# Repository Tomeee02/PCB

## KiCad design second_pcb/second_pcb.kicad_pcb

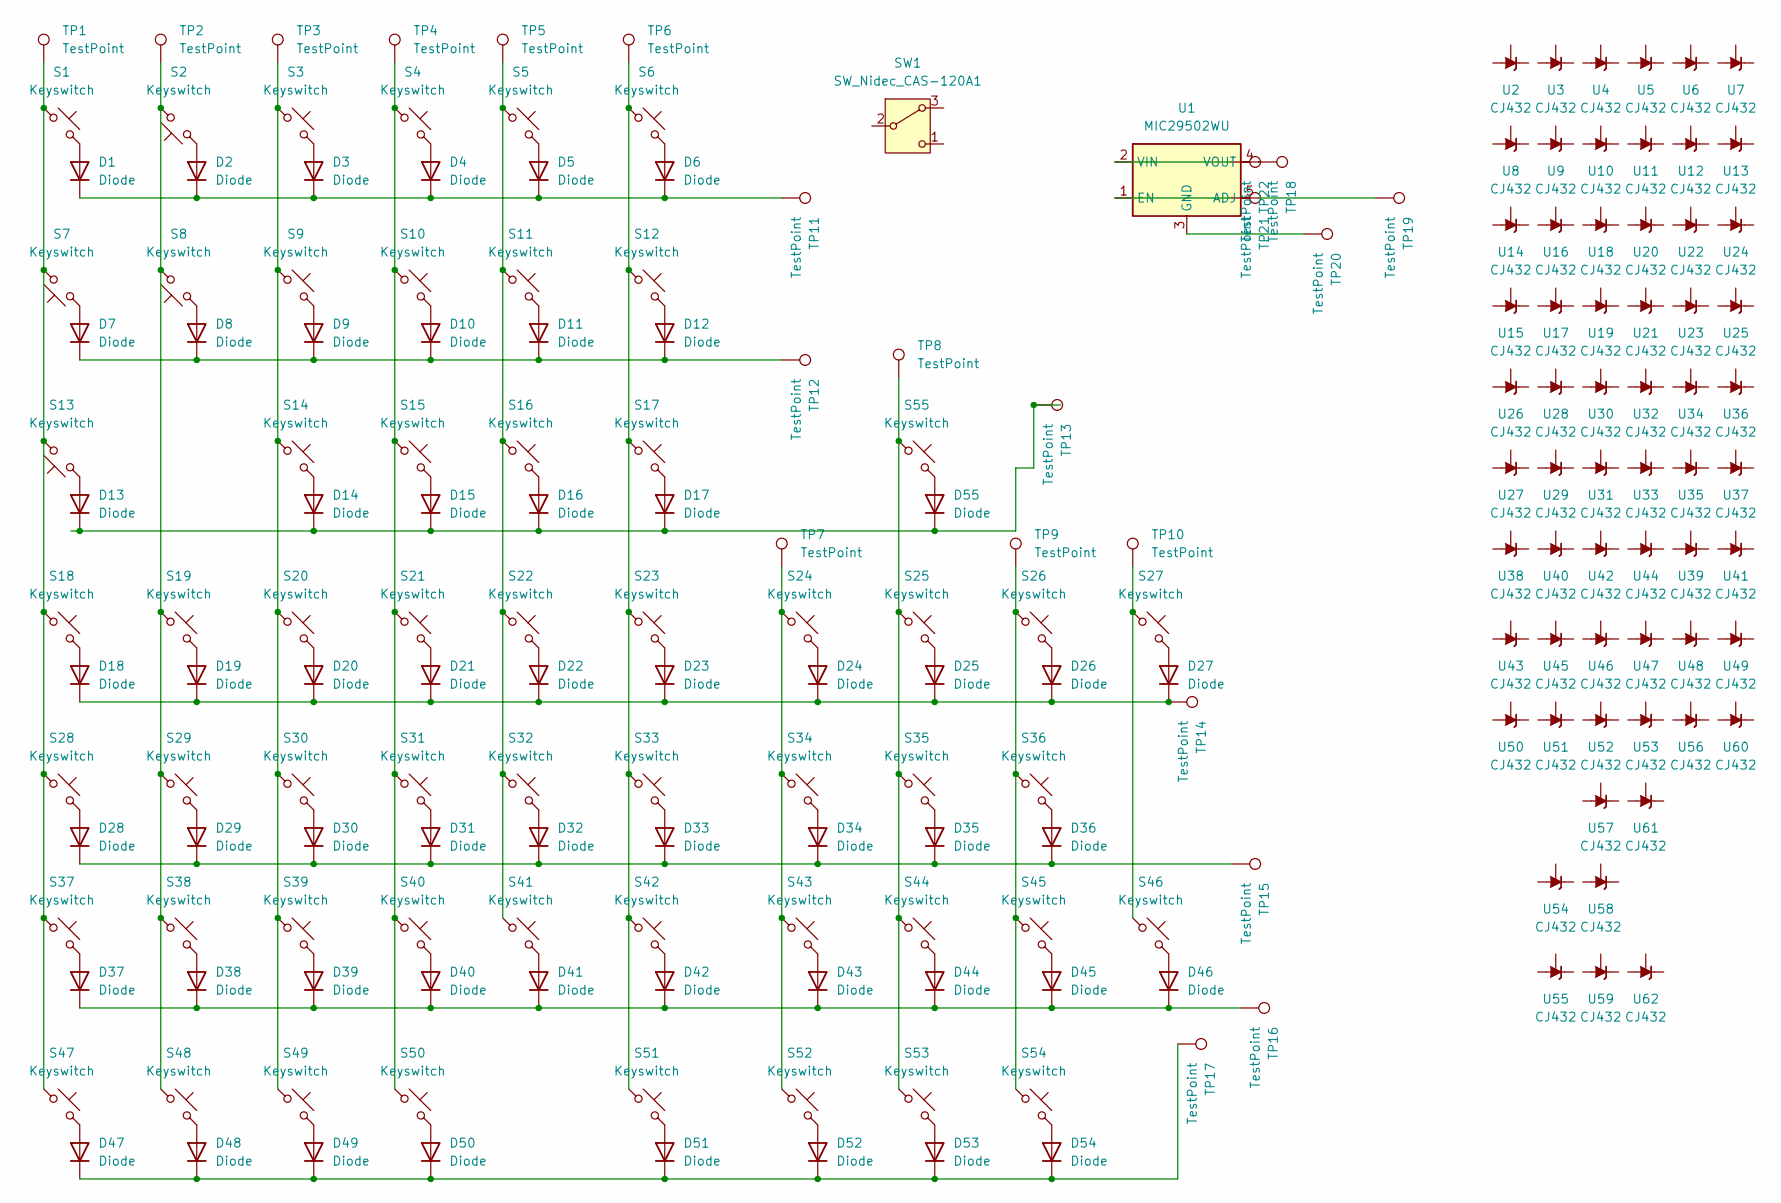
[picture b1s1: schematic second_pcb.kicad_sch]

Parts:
D1, D2, D3, D4, D5, D6, D7, D8, D9, D10, D11, D12, D13, D14, D15, D16, D17, D18, D19, D20, D21, D22, D23, D24, D25, D26, D27, D28, D29, D30, D31, D32, D33, D34, D35, D36, D37, D38, D39, D40, D41, D42, D43, D44, D45, D46, D47, D48, D49, D50, D51, D52, D53, D54, D55: Diode; D_PowerDI-123
S1, S46, S55: Keyswitch; 8mm
S2, S7, S8, S13: Keyswitch; Triangle
S3, S4, S5, S6, S9, S10, S11, S12, S14, S15, S16, S17, S18, S19, S20, S21, S22, S23, S24, S25, S26, S27, S28, S29, S30, S31, S32, S33, S34, S35, S36, S37, S38, S39, S40, S41, S42, S43, S44, S45, S47, S48, S49, S52, S53, S54: Keyswitch; 3rd
S50, S51: Keyswitch; oblong 230
SW1: SW_Nidec_CAS-120A1; Joystick
TP1, TP2, TP3, TP4, TP5, TP6, TP7, TP8, TP9, TP10, TP11, TP12, TP13, TP14, TP15, TP16, TP17, TP18, TP19, TP20, TP21, TP22: TestPoint; TestPoint_Pad_D1.5mm
U1: MIC29502WU; 0,5mm FPC Connector 5 pin
U2: CJ432; ,
U3: CJ432; -
U4: CJ432; .
U5: CJ432; 0
U6: CJ432; 1
U7: CJ432; 2
U8: CJ432; 3
U9: CJ432; 4
U10: CJ432; 5
U11: CJ432; 6
U12: CJ432; 7
U13: CJ432; 8
U14: CJ432; 9
U15: CJ432; A
U16: CJ432; Alt
U17: CJ432; B
U18: CJ432; Backslash
U19: CJ432; C
U20: CJ432; Ctrl
U21: CJ432; D
U22: CJ432; E
U23: CJ432; Enter
U24: CJ432; Esc
U25: CJ432; F
U26: CJ432; F1
U27: CJ432; F2
U28: CJ432; F3
U29: CJ432; F4
U30: CJ432; F5
U31: CJ432; F6
U32: CJ432; F7
U33: CJ432; F8
U34: CJ432; F9
U35: CJ432; F10
U36: CJ432; F11
U37: CJ432; F12
U38: CJ432; FN
U39: CJ432; G
U40: CJ432; H
U41: CJ432; I
U42: CJ432; J
U43: CJ432; K
U44: CJ432; L
U45: CJ432; M
U46: CJ432; N
U47: CJ432; O
U48: CJ432; P
U49: CJ432; Q
U50: CJ432; R
U51: CJ432; S
U52, U53: CJ432; Shift
U54: CJ432; T
U55: CJ432; Tab
U56: CJ432; U
U57: CJ432; V
U58: CJ432; W
U59: CJ432; X
U60: CJ432; Y
U61: CJ432; Z
U62: CJ432; LCD

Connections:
unnamed: D1.2 (A), S1.2
unnamed: D1.1 (K), D2.1 (K), D3.1 (K), D4.1 (K), D5.1 (K), D6.1 (K), TP11.1
unnamed: D2.2 (A), S2.1
unnamed: D3.2 (A), S3.2
unnamed: D4.2 (A), S4.2
unnamed: D5.2 (A), S5.2
unnamed: D6.2 (A), S6.2
unnamed: D7.2 (A), S7.1
unnamed: D8.2 (A), S8.1
unnamed: D9.2 (A), S9.2
unnamed: D10.2 (A), S10.2
unnamed: D7.1 (K), D8.1 (K), D9.1 (K), D10.1 (K), D11.1 (K), D12.1 (K), TP12.1
unnamed: D11.2 (A), S11.2
unnamed: D12.2 (A), S12.2
unnamed: D13.2 (A), S13.1
unnamed: D13.1 (K), D14.1 (K), D15.1 (K), D16.1 (K), D17.1 (K), D55.1 (K), TP13.1
unnamed: D14.2 (A), S14.2
unnamed: D15.2 (A), S15.2
unnamed: D16.2 (A), S16.2
unnamed: D17.2 (A), S17.2
unnamed: D18.2 (A), S18.2
unnamed: D18.1 (K), D19.1 (K), D20.1 (K), D21.1 (K), D22.1 (K), D23.1 (K), D24.1 (K), D25.1 (K), D26.1 (K), D27.1 (K), TP14.1
unnamed: D19.2 (A), S19.2
unnamed: D20.2 (A), S20.2
unnamed: D21.2 (A), S21.2
unnamed: D22.2 (A), S22.2
unnamed: D23.2 (A), S23.2
unnamed: D24.2 (A), S24.2
unnamed: D25.2 (A), S25.2
unnamed: D26.2 (A), S26.2
unnamed: D27.2 (A), S27.2
unnamed: D28.2 (A), S28.2
unnamed: D28.1 (K), D29.1 (K), D30.1 (K), D31.1 (K), D32.1 (K), D33.1 (K), D34.1 (K), D35.1 (K), D36.1 (K), TP15.1
unnamed: D29.2 (A), S29.2
unnamed: D30.2 (A), S30.2
unnamed: D31.2 (A), S31.2
unnamed: D32.2 (A), S32.2
unnamed: D33.2 (A), S33.2
unnamed: D34.2 (A), S34.2
unnamed: D35.2 (A), S35.2
unnamed: D36.2 (A), S36.2
unnamed: D37.2 (A), S37.2
unnamed: D37.1 (K), D38.1 (K), D39.1 (K), D40.1 (K), D41.1 (K), D42.1 (K), D43.1 (K), D44.1 (K), D45.1 (K), D46.1 (K), TP16.1
unnamed: D38.2 (A), S38.2
unnamed: D39.2 (A), S39.2
unnamed: D40.2 (A), S40.2
unnamed: D41.2 (A), S41.2
unnamed: D42.2 (A), S42.2
unnamed: D43.2 (A), S43.2
unnamed: D44.2 (A), S44.2
unnamed: D45.2 (A), S45.2
unnamed: D46.2 (A), S46.2
unnamed: D47.2 (A), S47.2
unnamed: D47.1 (K), D48.1 (K), D49.1 (K), D50.1 (K), D51.1 (K), D52.1 (K), D53.1 (K), D54.1 (K), TP17.1
unnamed: D48.2 (A), S48.2
unnamed: D49.2 (A), S49.2
unnamed: D50.2 (A), S50.2
unnamed: D51.2 (A), S51.2
unnamed: D52.2 (A), S52.2
unnamed: D53.2 (A), S53.2
unnamed: D54.2 (A), S54.2
unnamed: D55.2 (A), S55.2
unnamed: S1.1, S7.2, S13.2, S18.1, S28.1, S37.1, S47.1, TP1.1
unnamed: S4.1, S10.1, S15.1, S21.1, S31.1, S40.1, S50.1, TP4.1
unnamed: S5.1, S11.1, S16.1, S22.1, S32.1, S41.1, TP5.1
unnamed: S6.1, S12.1, S17.1, S23.1, S33.1, S42.1, S51.1, TP6.1
unnamed: S3.1, S9.1, S14.1, S20.1, S30.1, S39.1, S49.1, TP3.1
unnamed: S2.2, S8.2, S19.1, S29.1, S38.1, S48.1, TP2.1
unnamed: S24.1, S34.1, S43.1, S52.1, TP7.1
unnamed: S25.1, S35.1, S44.1, S53.1, S55.1, TP8.1
unnamed: S26.1, S36.1, S45.1, S54.1, TP9.1
unnamed: S27.1, S46.1, TP10.1
unnamed: TP19.1, U1.5 (ADJ)
unnamed: TP21.1, U1.1 (EN)
unnamed: TP20.1, U1.3 (GND)
unnamed: TP22.1, U1.2 (VIN)
unnamed: TP18.1, U1.4 (VOUT)

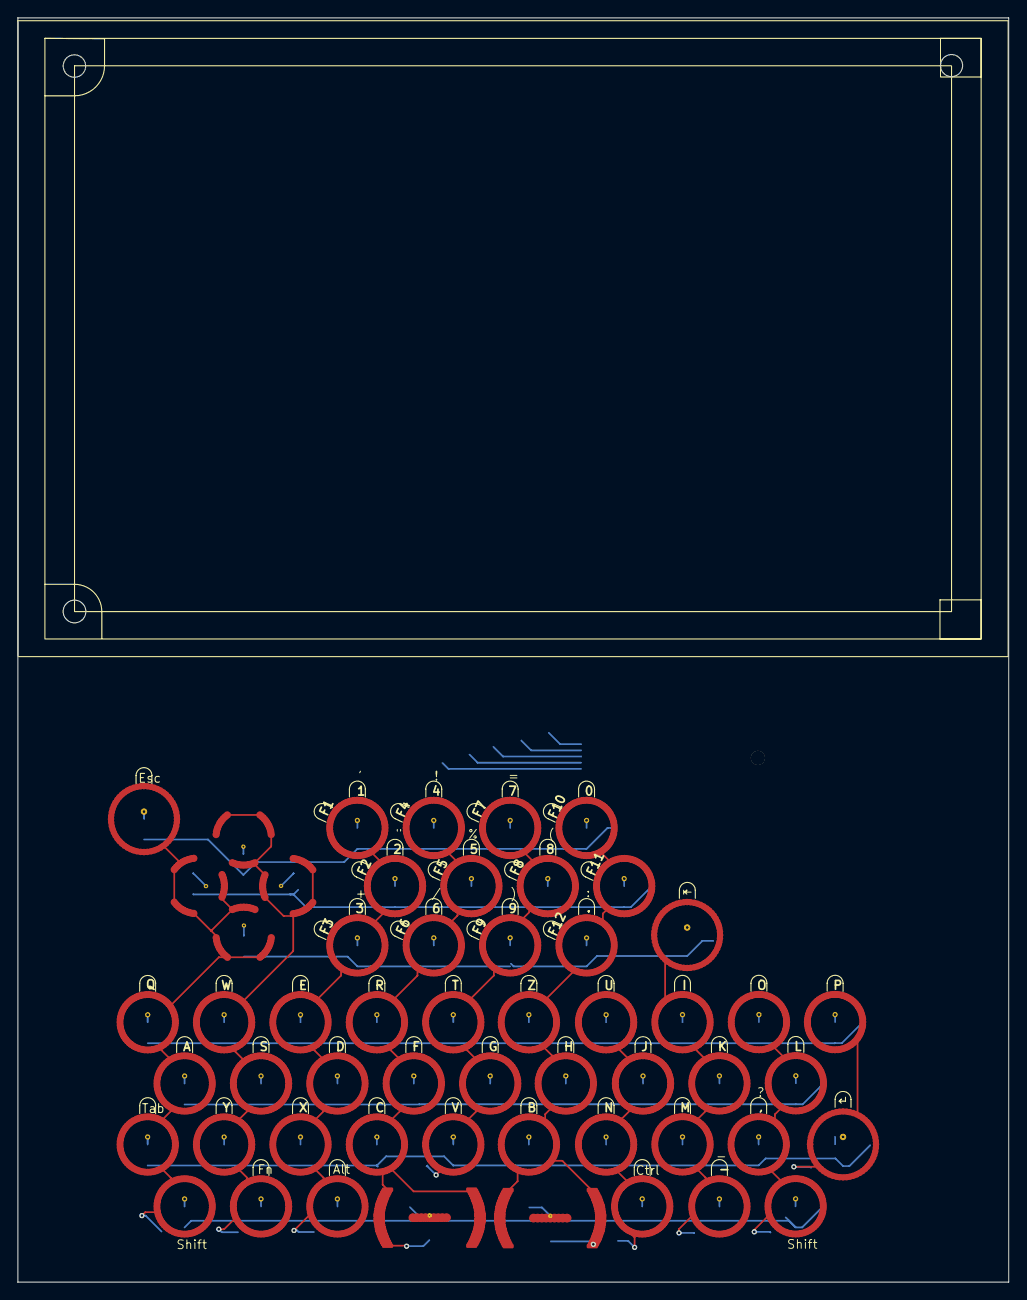
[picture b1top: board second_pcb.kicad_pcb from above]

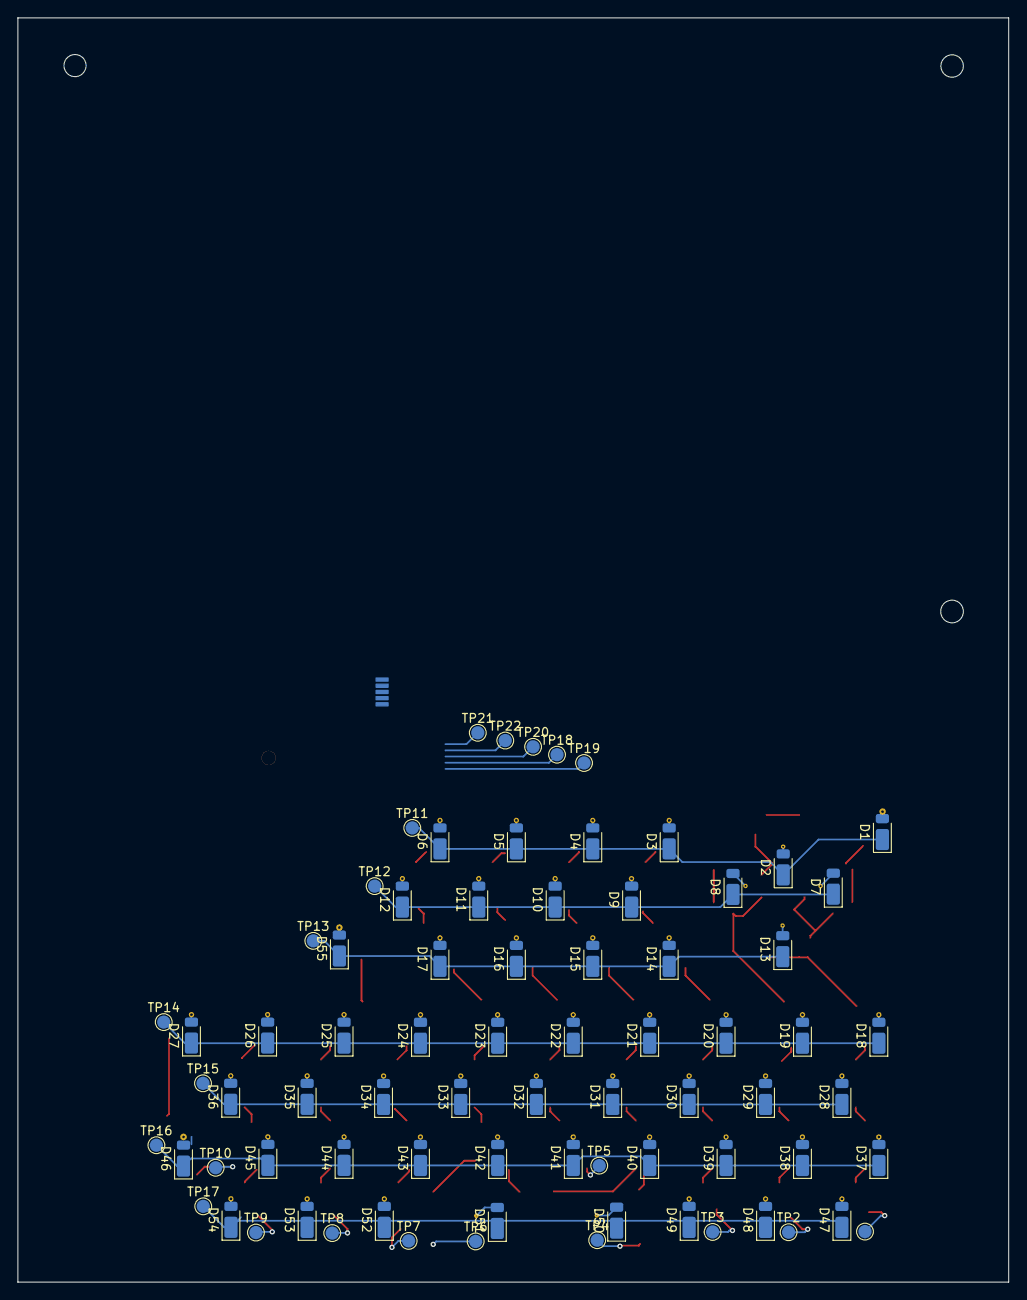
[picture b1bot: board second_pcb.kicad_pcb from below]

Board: 2 copper layers, 112.2 x 143.1 mm, 195 parts (77 on the bottom side), 77 nets.

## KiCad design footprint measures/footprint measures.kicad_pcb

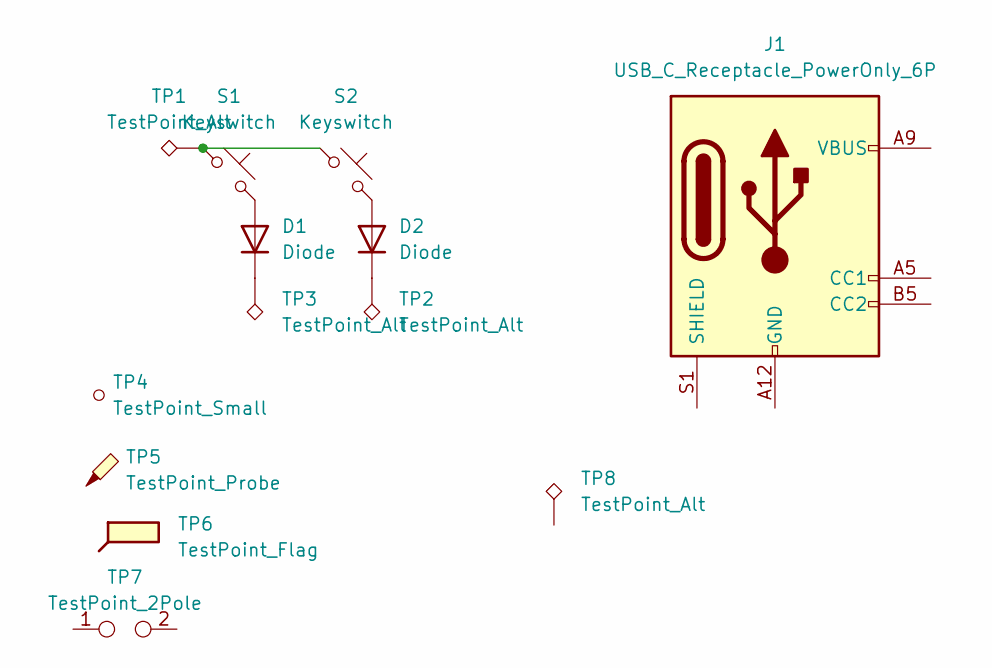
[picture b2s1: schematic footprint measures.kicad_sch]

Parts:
D1, D2: Diode; D_SOD-123
J1: USB_C_Receptacle_PowerOnly_6P; USB_C_Receptacle_GCT_USB4125-xx-x_6P_TopMnt_Horizontal
S1: Keyswitch; original 7mm
S2: Keyswitch; 1st 7mm
TP1: TestPoint_Alt; TestPoint_THTPad_3.0x3.0mm_Drill1.5mm
TP2, TP3: TestPoint_Alt; TestPoint_Pad_D1.5mm
TP4: TestPoint_Small; TestPoint_Keystone_5005-5009_Compact
TP5: TestPoint_Probe; TestPoint_Keystone_5010-5014_Multipurpose
TP6: TestPoint_Flag; TestPoint_THTPad_D3.0mm_Drill1.5mm
TP7: TestPoint_2Pole; TestPoint_2Pads_Pitch2.54mm_Drill0.8mm
TP8: TestPoint_Alt

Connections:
unnamed: D1.2 (A), S1.2
unnamed: D1.1 (K), TP3.1
unnamed: D2.2 (A), S2.2
unnamed: D2.1 (K), TP2.1
unnamed: J1.A12 (GND), J1.B12 (GND)
unnamed: J1.A9 (VBUS), J1.B9 (VBUS)
unnamed: S1.1, S2.1, TP1.1

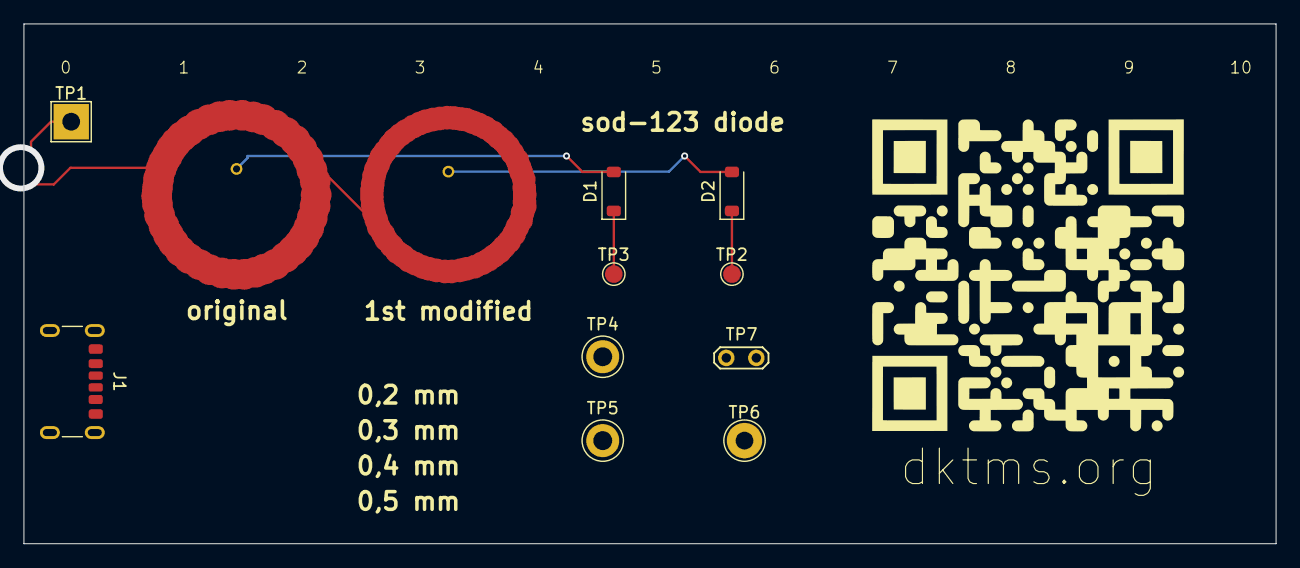
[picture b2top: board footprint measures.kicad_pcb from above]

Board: 2 copper layers, 106.0 x 44.0 mm, 12 parts (0 on the bottom side), 7 nets.

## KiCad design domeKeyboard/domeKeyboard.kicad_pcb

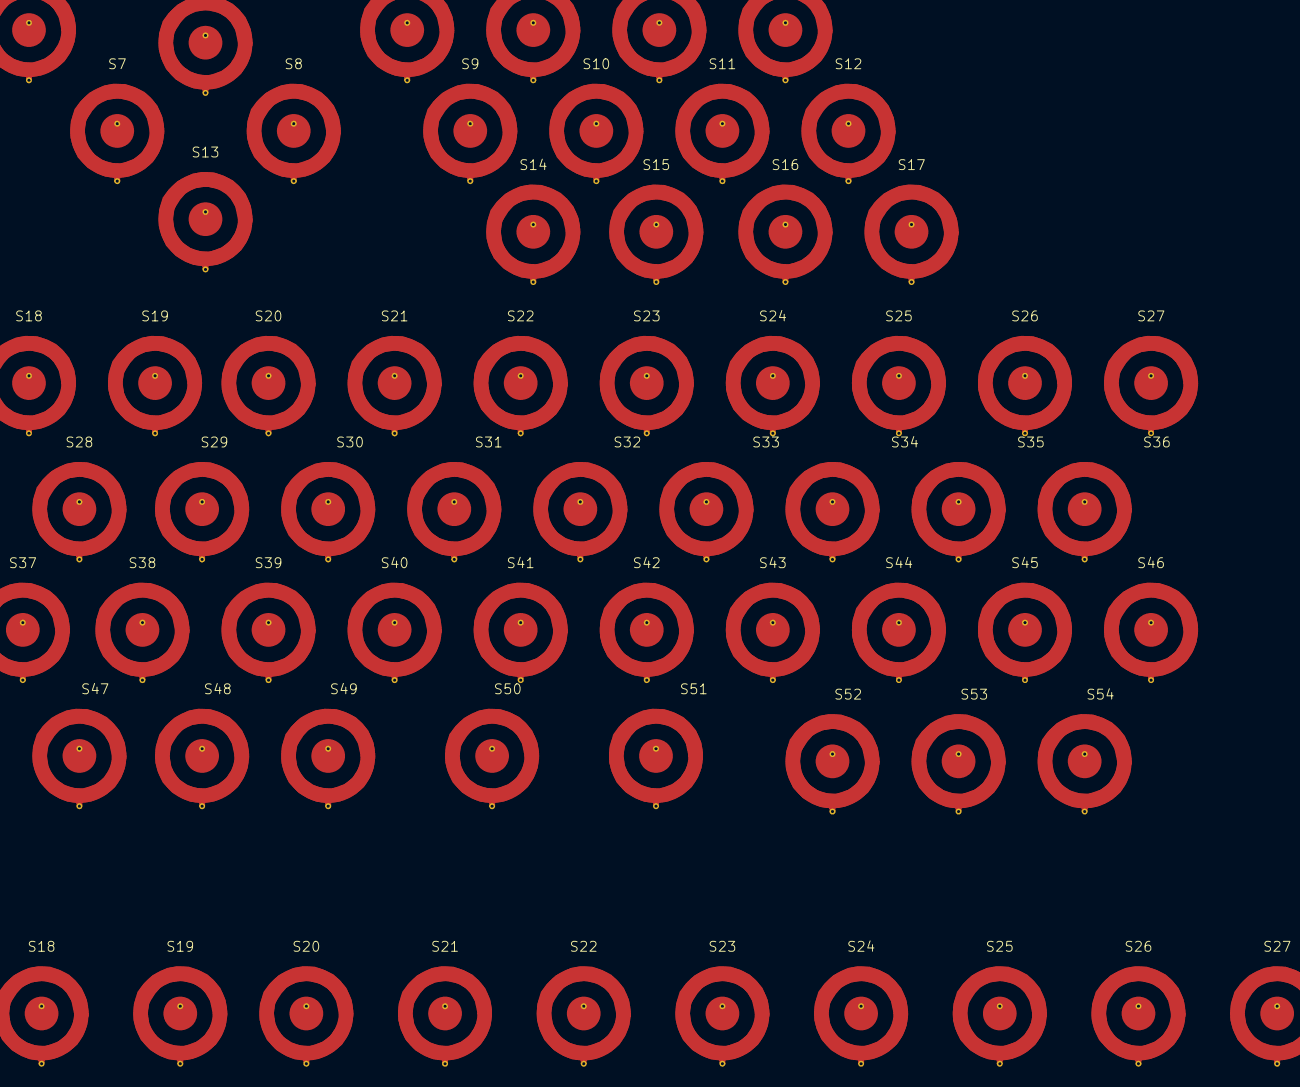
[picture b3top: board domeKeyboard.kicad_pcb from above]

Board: 2 copper layers, 64 parts (0 on the bottom side), 20 nets, no tracks yet.

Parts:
S1, S2, S3, S4, S5, S6, S7, S8, S9, S10, S11, S12, S13, S14, S15, S16, S17, S18, S18#2, S19, S19#2, S20, S20#2, S21, S21#2, S22, S22#2, S23, S23#2, S24, S24#2, S25, S25#2, S26, S26#2, S27, S27#2, S28, S29, S30, S31, S32, S33, S34, S35, S36, S37, S38, S39, S40, S41, S42, S43, S44, S45, S46, S47, S48, S49, S50, S51, S52, S53, S54: Keyswitch; DomeSwitch_8mm_double_sided

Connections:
unnamed: S18.2, S18#2.2
unnamed: S19.2, S19#2.2
unnamed: S20.2, S20#2.2
unnamed: S21.2, S21#2.2
unnamed: S22.2, S22#2.2
unnamed: S23.2, S23#2.2
unnamed: S24.2, S24#2.2
unnamed: S25.2, S25#2.2
unnamed: S26.2, S26#2.2
unnamed: S27.2, S27#2.2
unnamed: S1.1, S7.1, S13.1, S18.1, S18#2.1, S28.1, S37.1, S47.1
unnamed: S4.1, S10.1, S15.1, S21.1, S21#2.1, S31.1, S40.1, S50.1
unnamed: S5.1, S11.1, S16.1, S22.1, S22#2.1, S32.1, S41.1
unnamed: S6.1, S12.1, S17.1, S23.1, S23#2.1, S33.1, S42.1, S51.1
unnamed: S3.1, S9.1, S14.1, S20.1, S20#2.1, S30.1, S39.1, S49.1
unnamed: S2.1, S8.1, S19.1, S19#2.1, S29.1, S38.1, S48.1
unnamed: S24.1, S24#2.1, S34.1, S43.1, S52.1
unnamed: S25.1, S25#2.1, S35.1, S44.1, S53.1
unnamed: S26.1, S26#2.1, S36.1, S45.1, S54.1
unnamed: S27.1, S27#2.1, S46.1

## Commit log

2025-05-20 add fiverr folder
2025-05-21 add wiring and joystick_test file
2025-05-21 specify joystick_test file
2025-05-22 add images
2025-05-23 add documentation
2025-05-23 specify documentation
2025-05-25 add pico schematic
2025-05-27 add try folder
2025-05-27 add footprint
2025-05-28 add files
2025-05-29 new kicad file
2025-06-01 add layout for keyboard
2025-06-02 ordered pcb
2025-06-06 add idea picture
2025-06-07 add to doc
2025-06-08 extend doc
2025-06-09 doc extension
2025-06-11 doc extend
2025-06-12 add kicad new foldeer
2025-06-13 new folder
2025-08-03 design pcb
2025-08-04 add a lot of things
2025-08-05 full size keyboard
2025-08-06 add new keyboard
